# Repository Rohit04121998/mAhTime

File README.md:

# mAhTime

## Objective 

To calculate the battery life for a device using small batteries and in turn use the data to calculate for any bigger battery.

## Why do we need this?

The capacity of a battery is measured in Ah (ampere-hours, for large batteries) or mAh (milliampere-hours, for small batteries). This is usually mentioned on the battery or in the datasheets provided by the manufacturer. But the capacity changes depending on the age of the battery, operating conditions, slightly different chemical composition, etc. So it affects the final result.

To get the actual capacity (close-enough-value), measuring the same is the method. Different methods are there using which one can measure the capacity, for example, Coulomb counting, Voltage monitoring, etc. (Learn more here or here).

Here we use the second method; monitoring the terminal voltage when a known load (resistive) is connected.

## Method:

The batteries are charged and connected to a custom-designed shield for the ESP8266 microcontroller and a load is selected using a button. The microcontroller logs the terminal voltage read from its pin to the MQTT broker in RPi until the lower cut off voltage for the batteries is reached. The loads are automatically disconnected using logic level p-MOS switches. 

The values read by the microconttrollr is sent to a RPi using a MQTT broker named **mosquitto**. MQTT is a pub-sub based protocol where one device reads and sends the data to a topic and another device subscribes to the same topic to get the data published by the first device. A brief explanation of how values are sent via a broker is explained in the next heading. The recieved data is run through a python script to display the discharge curve and the area under the curve is calculated(area under the V*I v/s t curve is power rating and area under the I v/s t curve is the mAh / Ah of the batteries).

Once again the batteries are charged, but this time, Device Under Test (DUT) is selected instead of a load (using the same microcontroller). The time taken for the DUT to discharge the batteries is found. This can then be used to calculate the life of any battery using ratios ( Eg.: If for X (mAh) it is Y (no. of days) then for Z (mAh)? = YZ/X ).

## MQTT

MQTT is one of the most commonly used protocols in IoT projects. It stands for Message Queuing Telemetry Transport.

  In addition, it is designed as a lightweight messaging protocol that uses publish/subscribe operations to exchange data between clients and the server. Furthermore, its small size, low power usage, minimized data packets and ease of implementation make the protocol ideal of the “machine-to-machine” or “Internet of Things” world.

## WHY MQTT??

MQTT has unique features you can hardly find in other protocols, like:

* It’s a lightweight protocol. So, it’s easy to implement in software and fast in data transmission.
* It’s based on a messaging technique. You know how fast your messenger/WhatsApp message delivery is. MQTT protocol is a similar one.
* Minimized data packets. Hence, low network usage.
* Low power usage. As a result, it saves the connected device’s battery.

## How MQTT works
Like any other internet protocol, MQTT is based on clients and a server. The server is the guy who is responsible for handling the client’s requests of receiving or sending data between each other. MQTT server is called a broker and the clients are simply the connected devices.

#### So:

When a device (a client) wants to send data to the broker, we call this operation a *“Publish”* and the device *"Publisher"*.
When a device (a client) wants to receive data from the broker, we call this operation a *“Subscribe”* and this device as *"Subscriber"*.

 ## MQTT Components

* *Broker*, which is the server that handles the data transmission between the clients.
* A *Topic*, which is the place a device want to put or retrieve a message to/from.
* The *Message*, which is the data that a device receives “when subscribing” from a topic or send “when publishing” to a topic.
* *Publish*, is the process a device does to send its message to the broker.
* *Subscribe*, where a device does to retrieve a message from the broker.

*By now hopefully you would have an idea how a MQTT network might look or works like.* 

  The common methods used to transfer data are:
  
  * Making use of [test.mosquitto.org](http://test.mosquitto.org/) server as a MQTT broker and sending the data via this server.
  
  * Making use of a common WiFi network to share the data.
  
  * Making one of the ends (i.e either ESP8266 or the RPi) as an *Access Point* and connect the other to it.
  
    The 2nd and the 3rd methods do not use any online brokers. Therefore a broker is to be installed in the RPi. For information on how to install mosquitto broker on your RPi use the link [Getting Started with Mosquitto MQTT Broker on a Raspberry Pi](https://www.youtube.com/watch?v=AsDHEDbyLfg&t=72s).

## Hardware & Firmware:

A microcontroller unit (ESP8266-12E on LOLin board) has an inbuilt ADC (Analog to Digital Converter) with a precision of (1/1024)th of a volt. But the input voltage range is only 0 (0) - 1V (1024). To use this in 0 - 3V range a resistor voltage divider is implemented using precision resistors and an n- MOS switch to enable this voltage divider. The voltage divider is not the one which is present on the LOLin board. Those are not precision resistors, hence the readings may not be accurate. The n-MOS switch is required as the voltage divider acts as another resistive load parallel to the selected load. An OLED display is used to display the selected load, time, etc.

The hardware limits the maximum battery voltage to 3.6V as the battery voltage appears at pin A0 when voltage divider is disabled and the absolute maximum voltage given is 3.6V for ESP8266. The time taken for measurement is determined by the capacity of the battery and the chosen load.

The circuit connections and the designed PCB can be found in the directory PCB_KICAD. The details about the charger and the battery can be found in the 'Charger_hacked' directory. 
Arduino IDE is used to program the microcontroller. The required header files and libraries are in the *upload_voltage* directory.

### <p align="center">Fig 1. Unsoldered PCB</p>

PCB Front             |  PCB Back              
:-------------------------:|:-------------------------:
 |   

### <p align="center">Fig 2. Soldered PCB</p>

### <p align="center">Fig 3. Display</p>

## Code:

* In the *upload_voltage.ino* file, **Vbat** variable is used to store the voltage value. The queue is sized to hold a maximum of 1000 values. Here, the value is stored and sent every 4 seconds.

* To get the date and time info from the ESP8266, *NTTP Client* has been used . The *getFormattedDate()* function gives the date and time format as 2018-05-28T10:00:13Z. So modifications were done and the final output was  2018-05-28_10:00:13. This was further modified in the *plot.py* by replacing ':' with 'H', 'M' and 'S'. This was then appended to the *.csv* file having the load value as its initial name.

* The code is made such that a short press of the button is conssidered as next option and a long press is considered as select. The long press for one of the load values sets the value of variable *seleted* to a umber between 1 and 8. The load is selected according to the value of variable *selected* in the function *LoadVal*. The function *attachLoad* attaches the load and changes the state of the mosfets accordingly. The discharging of the battery starts as soon as the load is attached.

* Before any value is sent through MQTT, the variable *filename* which contains the device ID, load, date and time with the .csv extension is published to inform the subscriber that a new discharge cycle has started and to create a new CSV file by the name of the variable sent. Only after the filename are the voltage values to be sent.

* Once all the values are sent over through MQTT, a "Fully Discharged" message is sent stating that te experiment's finished.

* The code for MQTT subscribe is a simple code which tells the interpreter what to do when the connection with the MQTT broker is established and when a message is recieved. The funtion on_connect will be executed as soon as connection is established. The on_message funtion is executed as soon as a message is received. The messaged is checked for a **.csv** extension and a new CSV file is created if the result of this comparision is positive.

* This message with a .csv extension contains the ID of the device which published the message,the load selected, date and time of the moment a load is selected. The name of the new CSV file created contains only load,date and time(format containing 'H' 'M' and 'S' specified in one of the above points. Here data and time are included to differentiate between experiments conducted on the same day.

* The voltage values received are added to this file along with the time elapsed. At the end of the experiment "FUlly Discharged" message is recieved once and is added to the file informing the plotter that the experiment is finished and the mAh value can be calculated.

* In the script Plot_value.py **FuncAnimate** function is used to create an interactive mode i.e to plot a real time graph. The mAh value of the battery is shown only when the message "Fully Discharged" intercepts by the interpreter.

## Result:

  The result of the experments need not be the same everytime. The mAh value might change if the battery is not fully charged before the start of the experiment. The time taken for the discharge and the numbeer of voltage values recorded varies if a different load value is used or if the initial voltage of the battery is different.

The device was tested for 3 different loads and the graph plotted were as follows:

**Load**             |  093 Ohms             |  161 Ohms(Not fully charged)                                   
:-------------------------:|:-------------------------:|:-------------------------:
**Graph**|  | 

### <p align="center">232 Ohms</p>

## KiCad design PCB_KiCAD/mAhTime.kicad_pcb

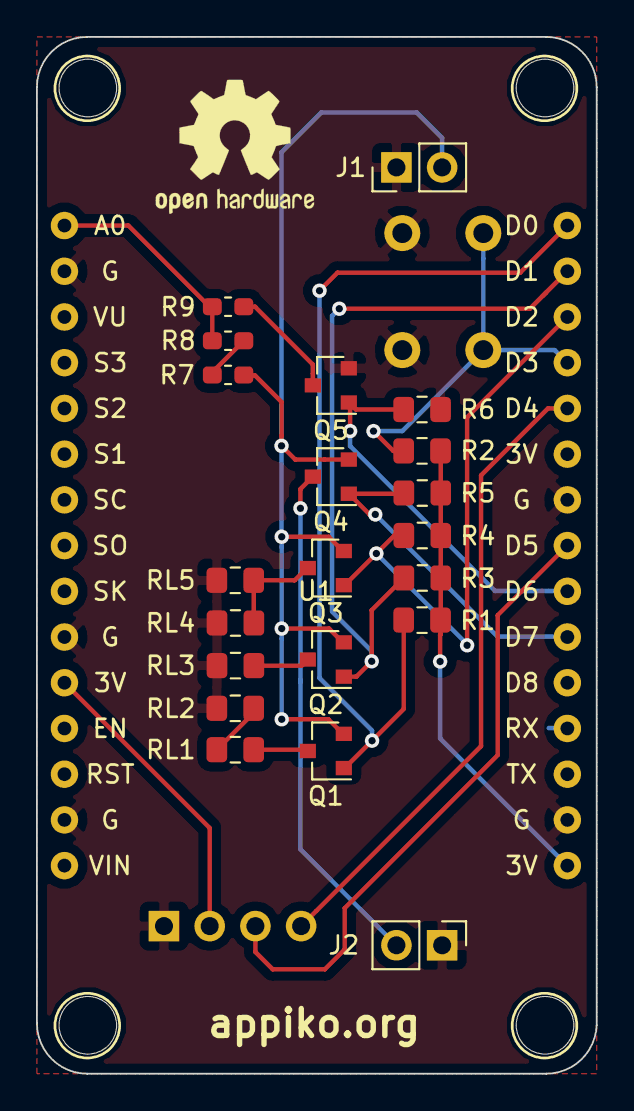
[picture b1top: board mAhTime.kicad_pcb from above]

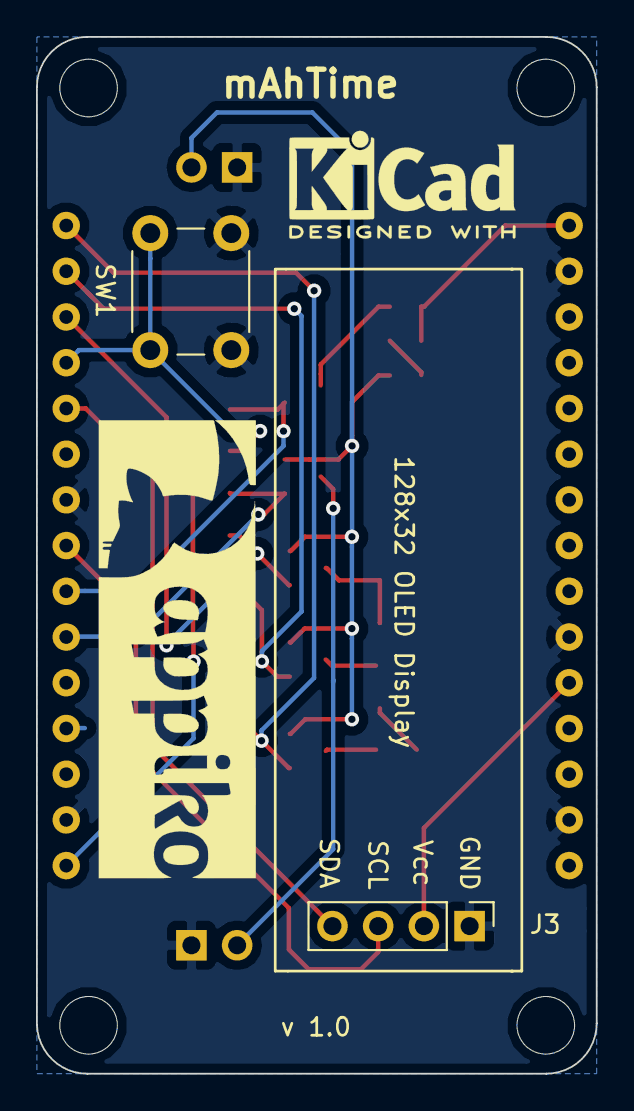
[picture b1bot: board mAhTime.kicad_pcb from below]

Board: 2 copper layers, 31.1 x 57.6 mm, 28 parts (2 on the bottom side), 19 nets.

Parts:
H1, H2, H3, H4: MountingHole; MountingHole_3.2mm_M3_ISO7380
J1: BATTERY; PinHeader_1x02_P2.54mm_Vertical
J2: DUT; PinHeader_1x02_P2.54mm_Vertical
J3: Conn_01x04; 128x32_OLED_Display
Q1, Q2, Q3, Q4: IRLML6401TRPBF; SOT-23
Q5: SI2302; SOT-23
R1, R3, R4, R5: 100k; R_0805_2012Metric_Pad1.15x1.40mm_HandSolder
R2: 1k; R_0805_2012Metric_Pad1.15x1.40mm_HandSolder
R6: 10k; R_0805_2012Metric_Pad1.15x1.40mm_HandSolder
R7, R8, R9: 30k; R_0603_1608Metric_Pad1.05x0.95mm_HandSolder
RL1, RL2, RL3, RL4, RL5: 232; R_0805_2012Metric_Pad1.15x1.40mm_HandSolder
SW1: SW_Push; SW_PUSH_6mm
U1: NodeMCU1.0(ESP-12E); NodeMCU-LoLinV3_without_border

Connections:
/Ctrl1: Q1.1, R1.2, U1.30
/Ctrl2: Q2.1, R3.2, U1.29
/Ctrl3: Q3.1, R4.2, U1.28
/Ctrl4: Q4.1, R5.2, U1.21
/En_VD: Q5.1, R6.2, U1.22
/SCL: J3.3, U1.23
/SDA: J3.4, U1.26
/SW: R2.2, SW1.1, U1.27
/Vbat: J1.2, Q1.2, Q2.2, Q3.2, Q4.2, R7.1
/Vcc: J3.2, R1.1, R2.1, R3.1, R4.1, R5.1, U1.11, U1.16, U1.25
/Vin: R8.2, R9.1, U1.1
/dut: J2.2, Q4.3
GND: J1.1, J2.1, J3.1, Q5.2, R6.1, RL2.2, RL3.2, RL4.2, RL5.2, SW1.2, U1.2, U1.10, U1.14, U1.17, U1.24
unnamed: Q1.3, RL1.1
unnamed: Q2.3, RL3.1
unnamed: Q3.3, RL4.1, RL5.1
unnamed: Q5.3, R9.2
unnamed: R7.2, R8.1
unnamed: RL1.2, RL2.1

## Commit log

2019-07-20 Add files via upload
    Added python,arduino and a CSV file
2019-07-20 Create hello
2019-07-23 Update README.md
    Image Editing
2019-07-23 Update README.md
    Added result graphs
